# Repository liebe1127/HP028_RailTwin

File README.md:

# 가변 계측–레일 이상 구간 디지털 트윈 기반 갠트리 크레인 안전관리 시스템

## 프로젝트 소개

본 프로젝트는 대형 갠트리 크레인이 **하부 주행 레일**을 따라 이동할 때 생기는 간격·충격·기울기·위치 데이터로, 이음부 단차·수직 변형·좌우 높이차를 구분해 웹 대시보드와 Unity WebGL에 표시하는 디지털 트윈입니다. 정상·주의·위험에 따라 평속·감속·정지를 정합니다. RBF는 쓰지 않습니다.

> **핵심 타겟:** 센서가 기록하는 이름은 **수직 변형**을 포함한 레일 기하입니다. 거더 변형·기초 침하·받침 열화는 그 원인입니다.

## 팀원 및 담당 역할

* **배용진:** SENSOR & EDGE (센서 데이터 획득, 교정, 축 정의)
* **배준호:** BACKEND & RULE ENGINE (비동기 수집, 4분류 규칙 판정)
* **김병서:** WEB & UNITY WEBGL (대시보드, 레일 3D)
* **김정우:** 조립·시험 (축소 모형, 반복 주행)

## 사용 하드웨어 및 기술 스택

* **현재 하드웨어 (Edge):** ESP32-S3-DevKitC-1 N16R8 1장. 좌·우 각 LR18-08U, MPU-6050, ADS1115, L298N, JGB37-520. 상세는 [`docs/hardware-configuration-history.md`](docs/hardware-configuration-history.md).
* **하드웨어 이력:** ESP32-C3 두 노드 펌웨어와 ESP32-S3-WROOM-1·ADXL345·HC-SR04 초기 스케치는 저장소에서 뺐다. 조립 실물에 올리는 코드는 `firmware/esp32_s3_rail_node/`이다.
* **백엔드 & 스트림:** Python, FastAPI, InfluxDB, ESP32 MQTT 업링크, 웹·Unity 다운링크 WebSocket.
* **판정:** 구간 특징 여섯 개로 이음부 단차·수직 변형·좌우 높이차. 웨이블릿·파고율·RBF는 쓰지 않음.
* **프론트엔드:** HTML/Vanilla JS, Tailwind CSS, Unity WebGL(레일만).

## 시스템 아키텍처 및 개발 로드맵

프로젝트는 총 4개의 Phase로 나뉩니다. 서버의 4분류 규칙 판정, InfluxDB 저장, 시연용 더미 스트리머와 웹·Unity 레일 뷰가 구현되어 있습니다. 조립 실물에 올리는 스케치는 `firmware/esp32_s3_rail_node/`이다.

### Phase 1: Sensor & Edge (실물 조립 완료)

* 실물 MCU는 ESP32-S3-DevKitC-1 1장이다. 좌·우 I2C 버스에 LR18-08U, MPU-6050, ADS1115를 각 1개 연결한다.
* `firmware/esp32_s3_rail_node/`는 가속도 3축, 자이로 3축, 칩 온도, 간격, 엔코더를 읽는다. 주행 중일 때만 MQTT 배치를 보낸다. BOOT는 전진 25초 후 정지한다.
* ESP32-S3-WROOM-1·ADXL345·HC-SR04 초기 스케치는 저장소에서 뺐다. 현재 보드와 다른 구성이다.

### Phase 2: Backend & Real-Time Data Stream (프로토타입 완료, 고도화 예정)

* **센서 업링크:** Wi-Fi MQTT QoS 1 → NCP Mosquitto → FastAPI 구독 → 비동기 Queue. 배치는 주행 중일 때만 온다.
* **분석 다운링크:** FastAPI → `/ws` → 웹 대시보드 / Unity WebGL.
* **시연:** `DEMO_MODE=true`일 때 1m 더미 레일의 20~25cm, 45~70cm, 80~90cm에 세 결함을 넣는다. 화면에는 시뮬레이션이라고 표시한다.

### Phase 3: Rule-Based Zone Detection (진행 중)

* 원시 간격을 구간 특징 `m`, `Δ`, `dm/dx`, `dΔ/dx`, `apeak`, `φ`로 만들어 `defects[]`와 단계 색 `rail_risk`를 낸다.
* 주의는 감속, 위험은 진입 전 정지. 정지 명령은 MQTT `.../command`이고, ESP32는 세로 충격만으로도 멈춘다.
* PyTorch RBF·`PRED_RAIL_DEFORM`·파고율은 목표 스택에서 제외.

### Phase 4: Web Dashboard & Unity Rails (진행 중)

* WebSocket 연동 실시간 웹 대시보드.
* Unity WebGL에 **레일만** 띄운다. 각 줄은 25×25 mm, 60 cm 아연 각파이프 3개를 이은 180 cm이다. 이상 구간 색과 갠트리 위치를 같은 좌표로 표시한다. 크레인 메시는 넣지 않는다.

## 프로토타입 실행 방법 (Getting Started)

1. **펌웨어:** `firmware/esp32_s3_rail_node/`에서 `secrets.h.example`을 `secrets.h`로 복사하고 와이파이와 MQTT 비밀번호를 넣는다. `secrets.h`는 커밋하지 않는다. 보드 ESP32S3 Dev Module, USB CDC로 업로드한다.
2. **환경 설정:** `.env.example`을 `.env`로 복사합니다. 실물 입력은 `DEMO_MODE=false`, 시연은 `DEMO_MODE=true`입니다.
3. **백엔드 가동:** `uvicorn main:app --host 0.0.0.0 --port 8000`
4. **센서/화면 접속:** ESP32는 `mqtt://223.130.128.198:1883`, 웹 대시보드는 `https://223.130.128.198:8000/dashboard` (`/ws`로 Unity·표가 같은 데이터를 받습니다).
5. **Unity WebGL (선택):** Mac 온보딩은 [`docs/mac-m5-unity-onboarding.md`](docs/mac-m5-unity-onboarding.md)입니다. 빌드는 `unity/RailTwinRails/README.md`대로 한 뒤 `scripts/sync_unity_webgl.sh`로 `frontend/unity/Build`에 복사합니다. 빌드 전에는 대시보드가 브라우저 레일 뷰를 씁니다.

## 개발보고서 및 AI 인계

* **판정 엔진 v2·AI 크기 추정 (기본 꺼짐):** [`docs/ai-judge.md`](docs/ai-judge.md), 좌표계 [`docs/coords-rail-sensor.md`](docs/coords-rail-sensor.md)
* **빌드·배포 대기 목록:** [`docs/빌드_대기_목록.md`](docs/빌드_대기_목록.md)
* **ESP32 MQTT 계약:** [`docs/esp32-mqtt-contract.md`](docs/esp32-mqtt-contract.md)
* **공식 PDF 양식 항목표:** [`docs/development-report-template-map.md`](docs/development-report-template-map.md)
* **프로젝트 통합 문맥:** [`docs/notion-project-context.md`](docs/notion-project-context.md)
* **센서 하드웨어 변경 이력:** [`docs/hardware-configuration-history.md`](docs/hardware-configuration-history.md)
* **Cursor·ChatGPT 인계 프롬프트:** [`docs/development-report-ai-handoff.md`](docs/development-report-ai-handoff.md)

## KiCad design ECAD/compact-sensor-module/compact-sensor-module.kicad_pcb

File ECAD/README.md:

# compact-sensor-module
- First pcb attempt : used [KiCAD](https://www.kicad.org/) 10.0.6
- Based on first prototype sensor module : not extensible. Left gpio pins didn't have interface.
- Already ordered 5 pics on [JLCPCB](https://jlcpcb.com/) (minimum oroder quantity) : **not PCBA**, need soldering by hand after shipping.
- Latest gerber in /output3 folder.
- 3d models, symbols, footprints for certain parts comes from [SnapMagic](https://www.snapeda.com/home/).

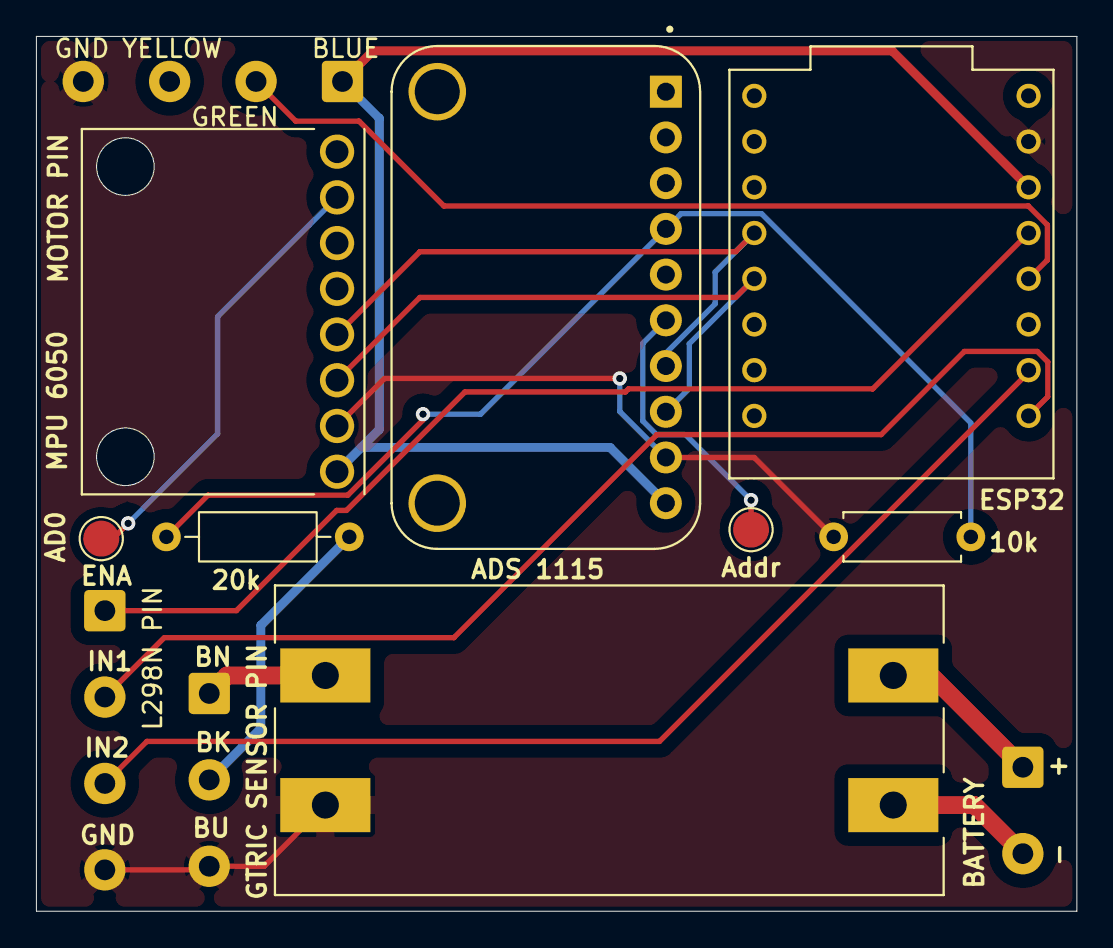
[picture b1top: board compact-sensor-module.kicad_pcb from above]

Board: 2 copper layers, 57.8 x 48.6 mm, 12 parts (0 on the bottom side), 15 nets.

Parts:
10k: 10k; R_Axial_DIN0207_L6.3mm_D2.5mm_P7.62mm_Horizontal
20k: 20k; R_Axial_DIN0207_L6.3mm_D2.5mm_P10.16mm_Horizontal
AD0: I2C Addr; TestPoint_Pad_D2.0mm
ADS 1115: ADS1115; MODULE_ZC261500
Addr: I2C Addr; TestPoint_Pad_D2.0mm
BATTERY: BATTERY PIN; SolderWire-0.5sqmm_1x02_P4.8mm_D0.9mm_OD2.3mm
ESP32: ESP32-C3_SUPERMINI_TH; MODULE_ESP32-C3_SUPERMINI_TH
GTRIC SENSOR PIN: GTRIC SENSOR PIN; SolderWire-0.5sqmm_1x03_P4.8mm_D0.9mm_OD2.3mm
L298N PIN: L298N PIN; SolderWire-0.5sqmm_1x04_P4.8mm_D0.9mm_OD2.3mm
MOTOR PIN: Motor Encoder Pin; SolderWire-0.5sqmm_1x04_P4.8mm_D0.9mm_OD2.3mm
MPU 6050: MPU-6050; MODULE_OC09600
U2: MT3608; MODULE_MT3608_DC-DC_STEP_UP_CONVERTER_2A_BOOSTER_MODULE

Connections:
/BAT+: BATTERY.1, U2.VIN_P (VIN+)
/BAT-: BATTERY.2, U2.VIN_N (VIN-)
/BK: 20k.1, GTRIC SENSOR PIN.2
/BLUE: ADS 1115.10 (VDD), ESP32.3.3 (3V3), MOTOR PIN.1, MPU 6050.VCC
/BN: GTRIC SENSOR PIN.1, U2.VOUT_P (VOUT+)
/ENA: ESP32.4 (GPIO4), L298N PIN.1
/GREEN: ESP32.3 (GPIO3), MOTOR PIN.2
/IN1: ESP32.0 (GPIO0), L298N PIN.2
/IN2: ESP32.1 (GPIO1), L298N PIN.3
/SCL: ADS 1115.8 (SCL), ESP32.9 (GPIO9), MPU 6050.SCL
/SDA: ADS 1115.7 (SDA), ESP32.8 (GPIO8), MPU 6050.SDA
GND: 10k.2, ADS 1115.9 (GND), ESP32.G (GND), GTRIC SENSOR PIN.3, L298N PIN.4, MOTOR PIN.4, MPU 6050.GND, U2.VOUT_N (VOUT-)
unnamed: AD0.1 (1_1), MPU 6050.AD0
unnamed: 10k.1, 20k.2, ADS 1115.4 (A0)
unnamed: ADS 1115.6 (ADDR), Addr.1 (1_1)
